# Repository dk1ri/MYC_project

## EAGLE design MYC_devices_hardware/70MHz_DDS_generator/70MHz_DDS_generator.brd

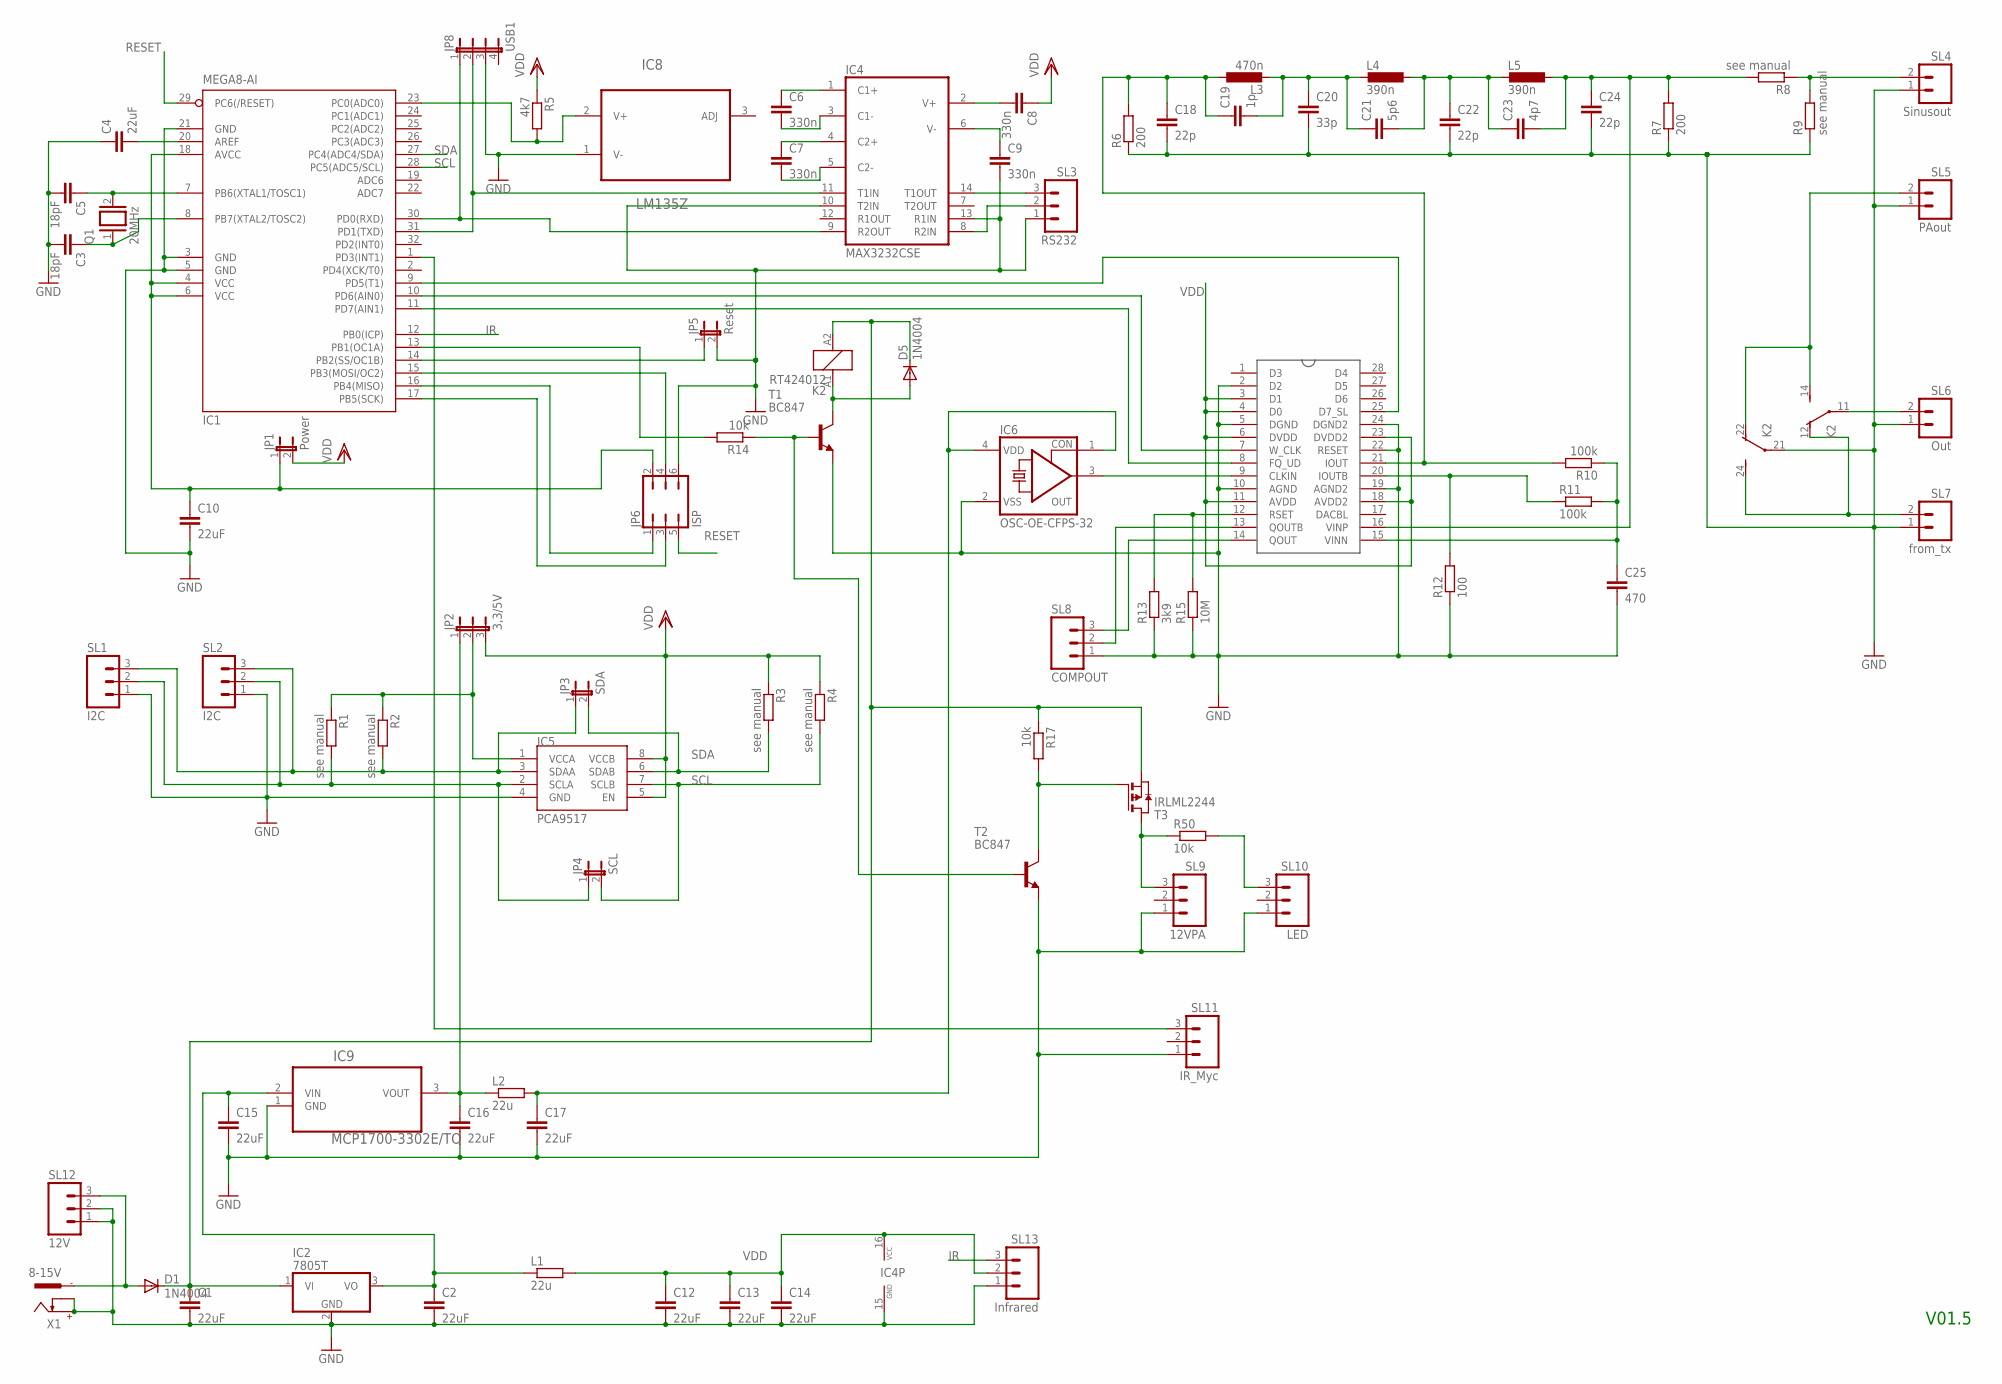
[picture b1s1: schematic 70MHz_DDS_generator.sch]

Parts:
C1, C2, C4, C10, C12, C13, C14, C15, C16, C17: 22uF; C1206
C3, C5: 18pF; C025-025X050
C6, C7, C8, C9: 330n; C1206
C18, C22, C24: 22p; C0805K
C19: 1p; C0805K
C20: 33p; C0805K
C21: 5p6; C0805K
C23: 4p7; C0805K
C25: 470; C1206
D1, D5: 1N4004; DO41-10
IC1: MEGA8-AI; TQFP32-08
IC2: 7805T; TO220H
IC4: MAX3232CSE; SO16
IC5: PCA9517; SO-08
IC6: OSC-OE-CFPS-32; 7.2X5.2-4-PAD
IC7: AD9851; SSOP28
IC8: LM135Z; TO127P254X533-3P
IC9: MCP1700-3302E/TO; TO127P254X495-3
JP1: Power; JP1
JP2: 3,3/5V; JP2
JP3: SDA; JP1
JP4: SCL; JP1
JP5: Reset; JP1
JP6: ISP; JP3Q
JP8: USB1; JP4
K2: RT424012; RT2C/O
L1, L2: 22u; R6332
L3: 470n; L4532M
L4, L5: 390n; L4532M
Q1: 20MHz; QS
R1, R2, R3, R4, R8, R9: see manual; R1206
R5: 4k7; R1206
R6, R7: 200; R1206
R10, R11: 100k; R1206
R12: 100; R1206
R13: 3k9; R1206
R14, R17, R50: 10k; R1206
R15: 10M; R1206
SL1, SL2: I2C; 03P
SL3: RS232; 03P
SL4: Sinusout; 02P
SL5: PAout; 02P
SL6: Out; 02P
SL7: from_tx; 02P
SL8: COMPOUT; 03P
SL9: 12VPA; 03P
SL10: LED; 03P
SL11: IR_Myc; 03P
SL12: 12V; 03P
SL13: Infrared; 03P
T1, T2: BC847; SOT23
T3: IRLML2244; SOT-23
X1: 8-15V; 737992-5

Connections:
GND: C1.2, C2.2, C3.2, C4.1, C5.2, C9.2, C10.2, C12.2, C13.2, C14.2, C15.2, C16.2, C17.2, C18.2, C20.2, C22.2, C24.2, C25.2, IC1.3 (GND), IC1.5 (GND), IC1.21 (GND), IC2.2 (GND), IC4.10 (T2IN), IC4.13 (R1IN), IC4.15 (GND), IC5.4 (GND), IC6.2 (VSS), IC7.2 (D2), IC7.5 (DGND), IC7.10 (AGND), IC7.19 (AGND2), IC7.22 (RESET), IC7.24 (DGND2), IC8.1 (V-), IC9.1 (GND), JP5.2, JP6.6, JP8.3, K2.21, R6.1, R7.1, R9.1, R12.1, R13.1, R15.1, SL1.1, SL2.1, SL3.1, SL4.1, SL5.1, SL6.1, SL7.1, SL8.1, SL9.1, SL10.1, SL11.1, SL12.1, SL12.2, SL13.1, T1.2 (E), T2.2 (E), X1.+, X1.K
IR: IC1.12 (PB0(ICP)), SL13.3
unnamed: IC1.9 (PD5(T1)), IC7.25 (D7_SL)
unnamed: C5.1, IC1.7 (PB6(XTAL1/TOSC1)), Q1.2
unnamed: C3.1, IC1.8 (PB7(XTAL2/TOSC2)), Q1.1
unnamed: C4.2, IC1.20 (AREF)
unnamed: IC5.3 (SDAA), JP3.1, R2.2, SL1.3, SL2.3
unnamed: IC1.16 (PB4(MISO)), JP6.1
unnamed: D1.A, SL12.3, X1.-1
unnamed: C10.1, IC1.4 (VCC), IC1.6 (VCC), IC1.18 (AVCC), JP1.1, JP6.2
unnamed: IC1.17 (PB5(SCK)), JP6.3
unnamed: IC1.14 (PB2(SS/OC1B)), JP5.1
unnamed: IC1.15 (PB3(MOSI/OC2)), JP6.4
unnamed: C7.2, IC4.5 (C2-)
unnamed: IC5.1 (VCCA), JP2.2, R1.1, R2.1
unnamed: IC5.2 (SCLA), JP4.1, R1.2, SL1.2, SL2.2
unnamed: IC4.14 (T1OUT), SL3.3
unnamed: C8.2, IC4.2 (V+)
unnamed: K2.12 (O), K2.24 (S), SL7.2
unnamed: C2.1, C15.1, IC2.3 (VO), IC9.2 (VIN), L1.1
unnamed: IC1.10 (PD6(AIN0)), IC7.7 (W_CLK)
unnamed: IC4.8 (R2IN), SL3.2
unnamed: R50.2, SL10.3
unnamed: C7.1, IC4.4 (C2+)
unnamed: K2.14 (S), K2.22 (O), SL5.2
unnamed: C21.2, C22.1, C23.1, L4.1, L5.2
unnamed: C17.1, IC6.1 (CON), IC6.4 (VDD), L2.2
unnamed: C18.1, C19.1, IC7.21 (IOUT), L3.1, R6.2, R10.2
unnamed: C19.2, C20.1, C21.1, L3.2, L4.2
unnamed: C9.1, IC4.6 (V-)
unnamed: IC1.11 (PD7(AIN1)), IC7.8 (FQ_UD)
unnamed: IC6.3 (OUT), IC7.9 (CLKIN)
unnamed: R14.1, T1.1 (B), T2.1 (B)
unnamed: C23.2, C24.1, IC7.16 (VINP), L5.1, R7.2, R8.2
unnamed: IC1.30 (PD0(RXD)), IC4.9 (R2OUT), JP8.1
unnamed: D5.A, K2.A1 (1), T1.3 (C)
unnamed: IC7.12 (RSET), R13.2, R15.2
unnamed: C25.1, IC7.15 (VINN), R10.1, R11.2
unnamed: IC7.14 (QOUT), SL8.3
unnamed: IC1.23 (PC0(ADC0)), IC8.2 (V+), R5.2
unnamed: IC7.20 (IOUTB), R11.1, R12.2
unnamed: K2.11, SL6.2
unnamed: R50.1, SL9.3, T3.1 (D)
unnamed: R17.2, T2.3 (C), T3.3 (G)
unnamed: IC1.31 (PD1(TXD)), IC4.11 (T1IN), JP8.2
unnamed: IC1.13 (PB1(OC1A)), R14.2
unnamed: C1.1, D1.C, D5.C, IC2.1 (VI), K2.A2 (2), R17.1, T3.2 (S)
unnamed: IC1.1 (PD3(INT1)), SL11.3
unnamed: C6.1, IC4.1 (C1+)
unnamed: IC7.13 (QOUTB), SL8.2
unnamed: R8.1, R9.2, SL4.2
unnamed: C6.2, IC4.3 (C1-)
unnamed: C16.1, IC9.3 (VOUT), JP2.1, L2.1
RESET: IC1.29 (PC6(/RESET)), JP6.5
SCL: IC1.28 (PC5(ADC5/SCL)), IC5.7 (SCLB), JP4.2, R4.2
SDA: IC1.27 (PC4(ADC4/SDA)), IC5.6 (SDAB), JP3.2, R3.2
VDD: C8.1, C12.1, C13.1, C14.1, IC4.16 (VCC), IC5.5 (EN), IC5.8 (VCCB), IC7.3 (D1), IC7.4 (D0), IC7.6 (DVDD), IC7.11 (AVDD), IC7.18 (AVDD2), IC7.23 (DVDD2), JP1.2, JP2.3, L1.2, R3.1, R4.1, R5.1, SL13.2

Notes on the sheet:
V01.5

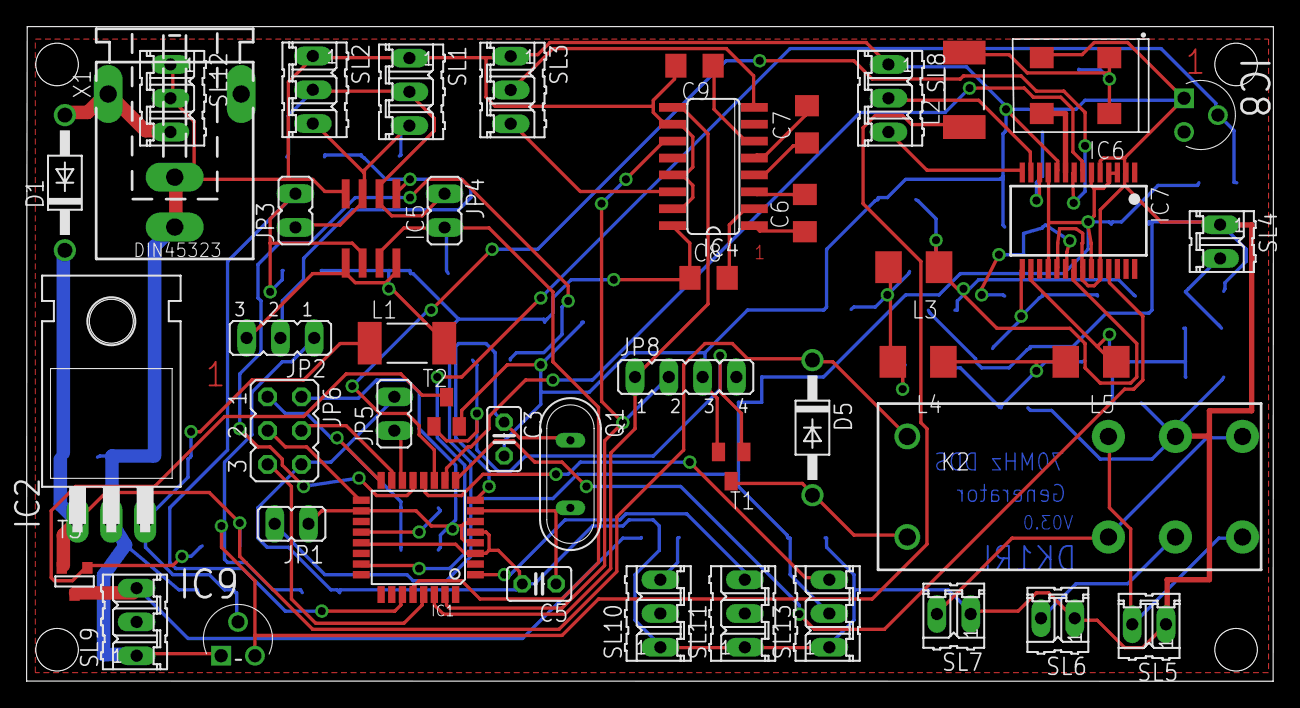
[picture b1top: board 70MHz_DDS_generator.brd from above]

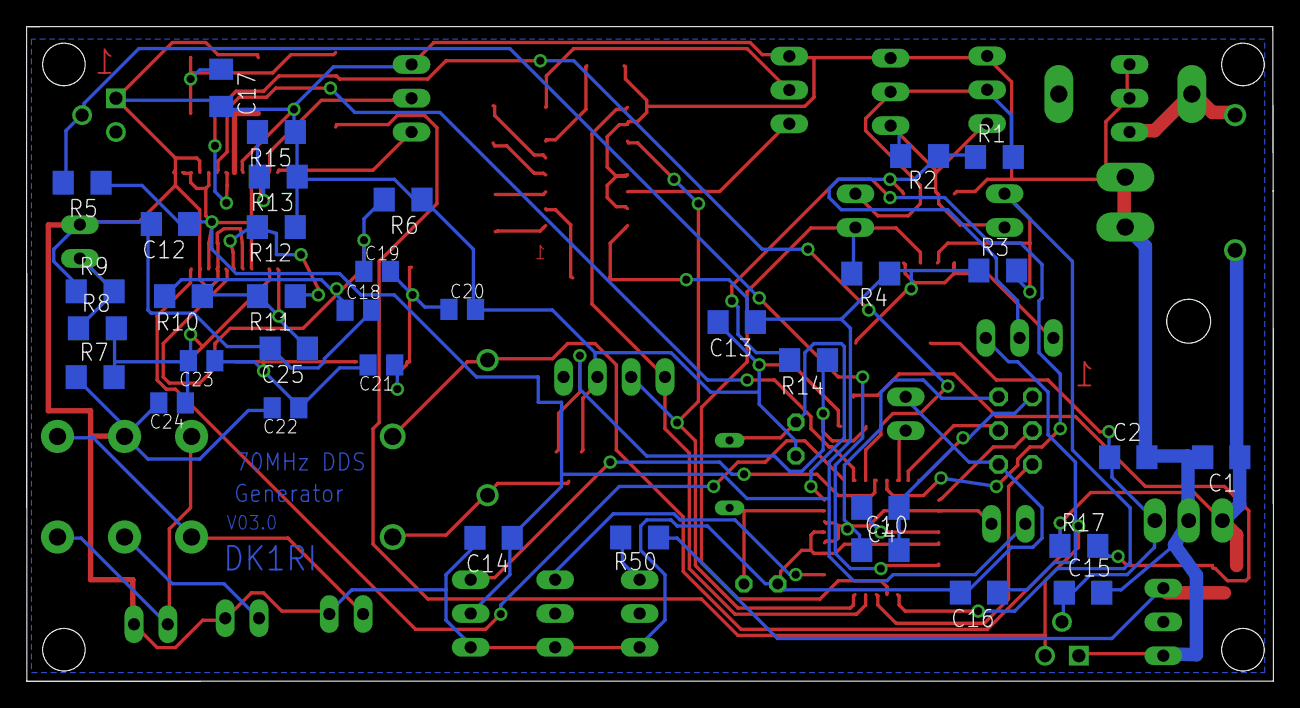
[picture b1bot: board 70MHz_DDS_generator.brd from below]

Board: 3 copper layers, 93.7 x 49.2 mm, 82 parts (35 on the bottom side), 57 nets.

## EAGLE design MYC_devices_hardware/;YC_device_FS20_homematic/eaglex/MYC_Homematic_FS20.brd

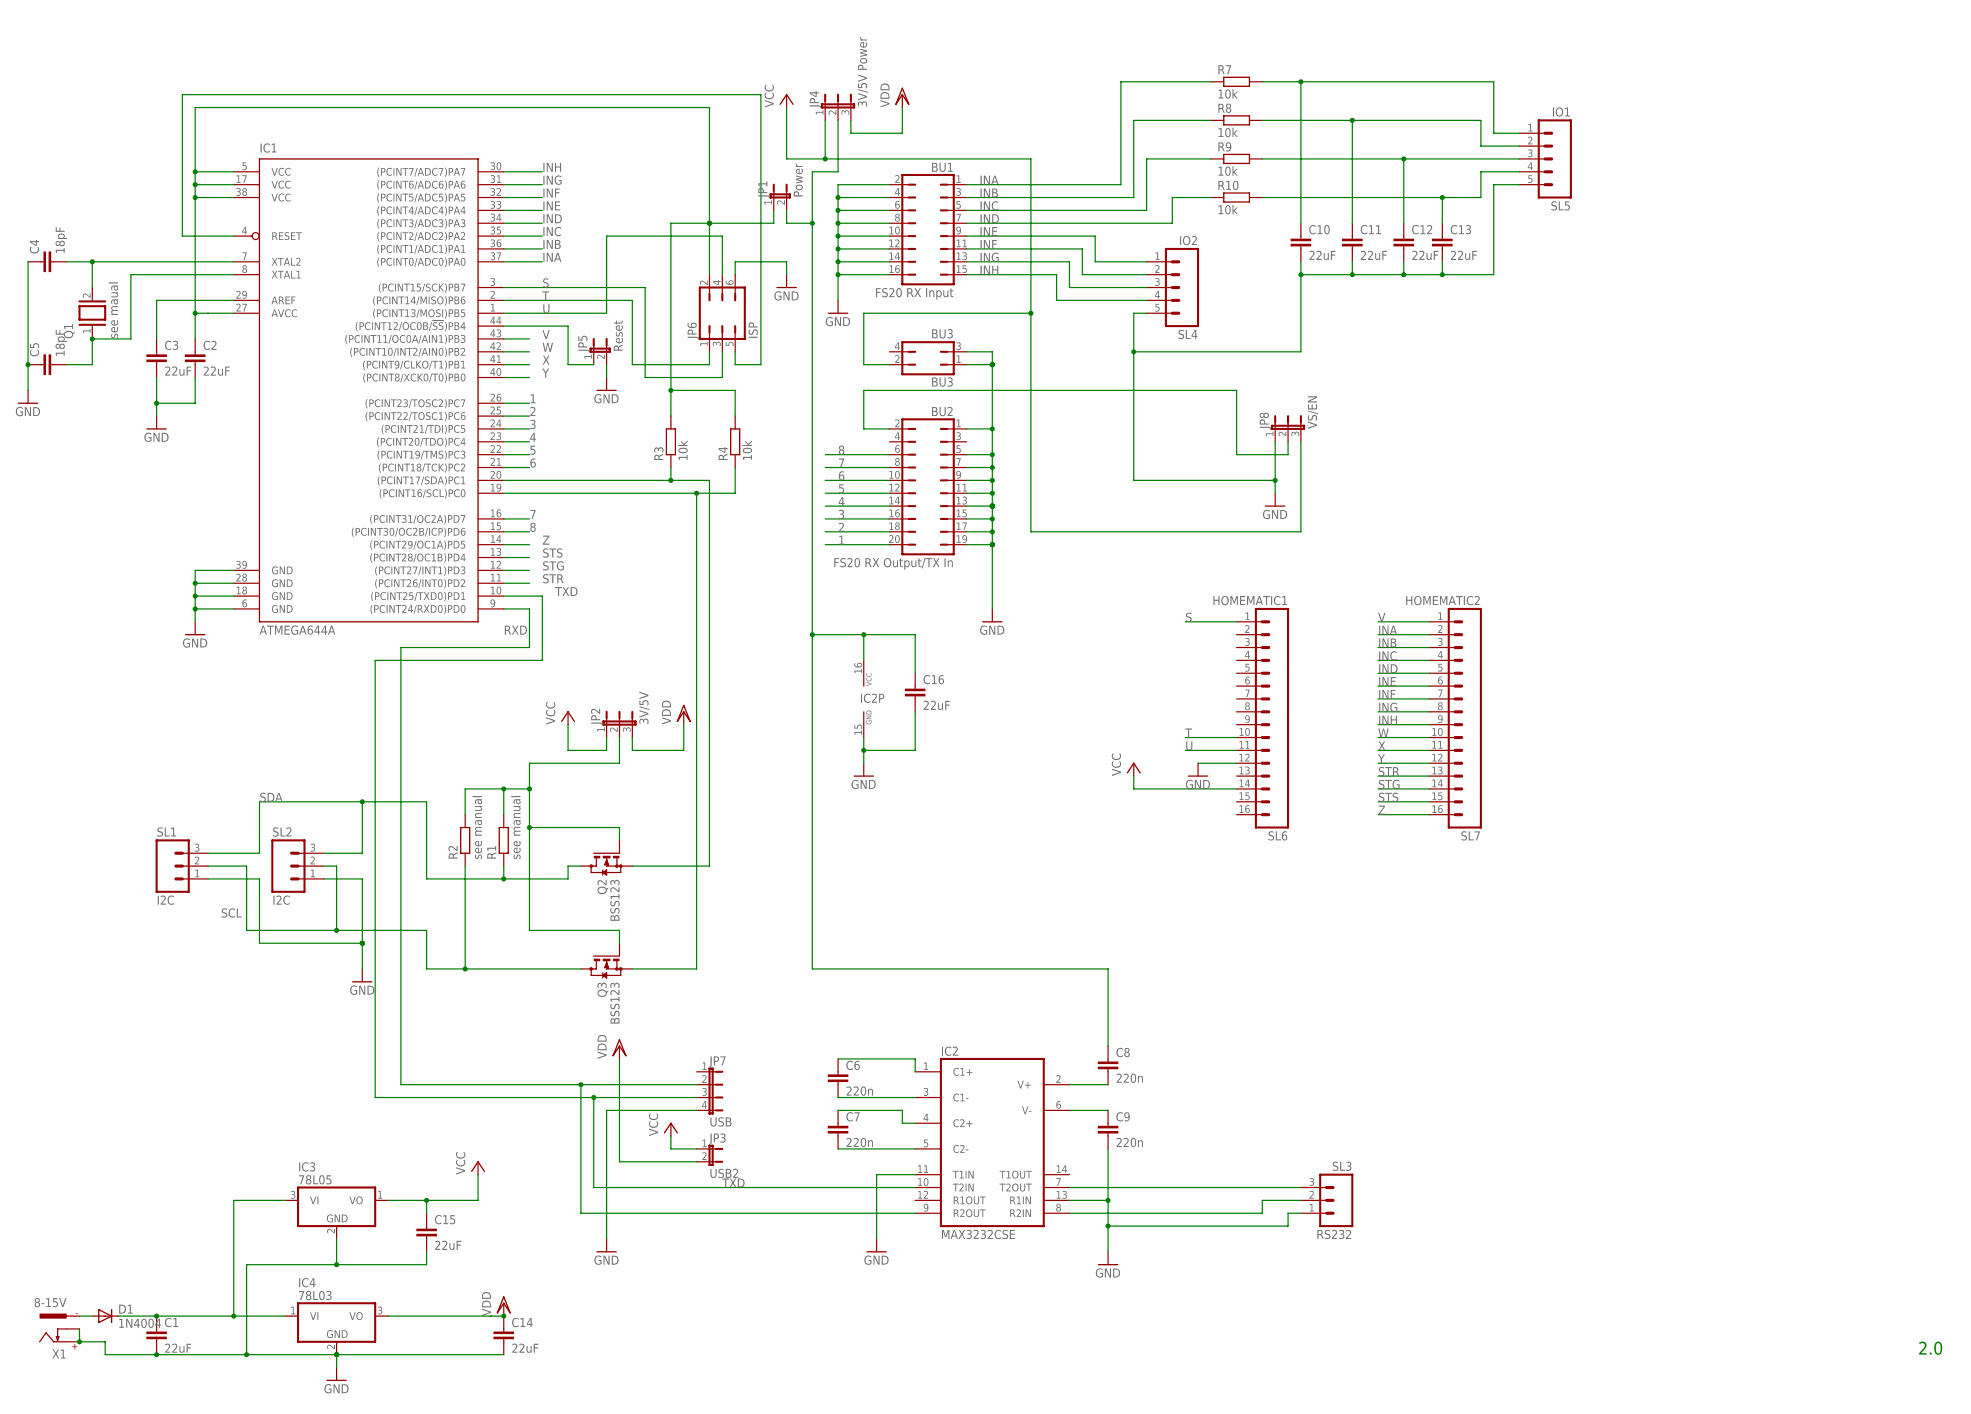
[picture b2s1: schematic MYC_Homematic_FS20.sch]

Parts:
BU1: FS20 RX Input; JP8Q
BU2: FS20 RX Output/TX In; JP10Q
BU3: BU3; JP2Q
C1, C2, C3, C10, C11, C12, C13, C14, C15, C16: 22uF; C1206
C4, C5: 18pF; C025-030X050
C6, C7, C8, C9: 220n; C1206
D1: 1N4004; DO41-10
IC1: ATMEGA644A; TQFP44
IC2: MAX3232CSE; SO16
IC3: 78L05; TO92
IC4: 78L03; TO220V
JP1: Power; JP1
JP2: 3V/5V; JP2
JP3: USB2; JP1
JP4: 3V/5V Power; JP2
JP5: Reset; JP1
JP6: ISP; JP3Q
JP7: USB; JP4
JP8: VS/EN; JP2
Q1: see maual; QS
Q2, Q3: BSS123; SOT23
R1, R2: see manual; R1206
R3, R4, R7, R8, R9, R10: 10k; R1206
SL1, SL2: I2C; 03P
SL3: RS232; 03P
SL4: IO2; 05P
SL5: IO1; 05P
SL6: HOMEMATIC1; 16P
SL7: HOMEMATIC2; 16P
X1: 8-15V; 737992-5

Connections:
1: BU2.20, IC1.26 ((PCINT23/TOSC2)PC7)
2: BU2.18, IC1.25 ((PCINT22/TOSC1)PC6)
3: BU2.16, IC1.24 ((PCINT21/TDI)PC5)
4: BU2.14, IC1.23 ((PCINT20/TDO)PC4)
5: BU2.12, IC1.22 ((PCINT19/TMS)PC3)
6: BU2.10, IC1.21 ((PCINT18/TCK)PC2)
7: BU2.8, IC1.16 ((PCINT31/OC2A)PD7)
8: BU2.6, IC1.15 ((PCINT30/OC2B/ICP)PD6)
C13: C6.1, IC2.1 (C1+)
GND: BU1.2, BU1.4, BU1.6, BU1.8, BU1.10, BU1.12, BU1.14, BU1.16, BU2.1, BU2.5, BU2.7, BU2.9, BU2.11, BU2.13, BU2.15, BU2.17, BU2.19, BU3.1, BU3.3, C1.2, C2.2, C3.2, C4.1, C5.1, C9.2, C10.2, C11.2, C12.2, C13.2, C14.2, C15.2, C16.2, IC1.6 (GND), IC1.18 (GND), IC1.28 (GND), IC1.39 (GND), IC2.11 (T1IN), IC2.13 (R1IN), IC2.15 (GND), IC3.2 (GND), IC4.2 (GND), JP5.2, JP6.6, JP7.4, JP8.1, SL1.1, SL2.1, SL3.1, SL4.5, SL5.5, SL6.12, X1.+, X1.K
INA: BU1.1, IC1.37 ((PCINT0/ADC0)PA0), R7.1, SL7.2
INB: BU1.3, IC1.36 ((PCINT1/ADC1)PA1), R8.1, SL7.3
INC: BU1.5, IC1.35 ((PCINT2/ADC2)PA2), R9.1, SL7.4
IND: BU1.7, IC1.34 ((PCINT3/ADC3)PA3), R10.1, SL7.5
INE: BU1.9, IC1.33 ((PCINT4/ADC4)PA4), SL4.1, SL7.6
INF: BU1.11, IC1.32 ((PCINT5/ADC5)PA5), SL4.2, SL7.7
ING: BU1.13, IC1.31 ((PCINT6/ADC6)PA6), SL4.3, SL7.8
INH: BU1.15, IC1.30 ((PCINT7/ADC7)PA7), SL4.4, SL7.9
unnamed: C1.1, D1.C, IC3.3 (VI), IC4.1 (VI)
unnamed: IC1.44 ((PCINT12/OC0B/!SS!)PB4), JP5.1
unnamed: C7.2, IC2.5 (C2-)
unnamed: JP2.2, Q2.1 (G), Q3.1 (G), R1.2, R2.2
unnamed: IC1.19 ((PCINT16/SCL)PC0), Q3.2 (S), R4.1
unnamed: C3.1, IC1.29 (AREF)
unnamed: C2.1, IC1.5 (VCC), IC1.17 (VCC), IC1.27 (AVCC), IC1.38 (VCC), JP1.1, JP6.2, R3.2, R4.2
unnamed: IC1.20 ((PCINT17/SDA)PC1), Q2.2 (S), R3.1
unnamed: BU2.2, JP8.2
unnamed: D1.A, X1.-1
unnamed: IC2.8 (R2IN), SL3.2
unnamed: C7.1, IC2.4 (C2+)
unnamed: C6.2, IC2.3 (C1-)
unnamed: C10.1, R7.2, SL5.1
unnamed: C8.2, IC2.2 (V+)
unnamed: C9.1, IC2.6 (V-)
unnamed: C11.1, R8.2, SL5.2
unnamed: C4.2, IC1.7 (XTAL2), Q1.2
unnamed: C12.1, R9.2, SL5.3
unnamed: C13.1, R10.2, SL5.4
unnamed: C8.1, C16.1, IC2.16 (VCC), JP1.2, JP4.2
unnamed: IC1.4 (RESET), JP6.5
unnamed: IC2.7 (T2OUT), SL3.3
unnamed: C5.2, IC1.8 (XTAL1), Q1.1
RXD: IC1.9 ((PCINT24/RXD0)PD0), IC2.9 (R2OUT), JP7.2
S: IC1.3 ((PCINT15/SCK)PB7), JP6.3, SL6.1
SCL: Q3.3 (D), R2.1, SL1.2, SL2.2
SDA: Q2.3 (D), R1.1, SL1.3, SL2.3
STG: IC1.12 ((PCINT27/INT1)PD3), SL7.14
STR: IC1.11 ((PCINT26/INT0)PD2), SL7.13
STS: IC1.13 ((PCINT28/OC1B)PD4), SL7.15
T: IC1.2 ((PCINT14/MISO)PB6), JP6.1, SL6.10
TXD: IC1.10 ((PCINT25/TXD0)PD1), IC2.10 (T2IN), JP7.3
U: IC1.1 ((PCINT13/MOSI)PB5), JP6.4, SL6.11
V: IC1.43 ((PCINT11/OC0A/AIN1)PB3), SL7.1
VCC: BU3.2, C15.1, IC3.1 (VO), JP2.1, JP3.1, JP4.1, JP8.3, SL6.14
VDD: C14.1, IC4.3 (VO), JP2.3, JP3.2, JP4.3
W: IC1.42 ((PCINT10/INT2/AIN0)PB2), SL7.10
X: IC1.41 ((PCINT9/CLKO/T1)PB1), SL7.11
Y: IC1.40 ((PCINT8/XCK0/T0)PB0), SL7.12
Z: IC1.14 ((PCINT29/OC1A)PD5), SL7.16

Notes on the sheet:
2.0

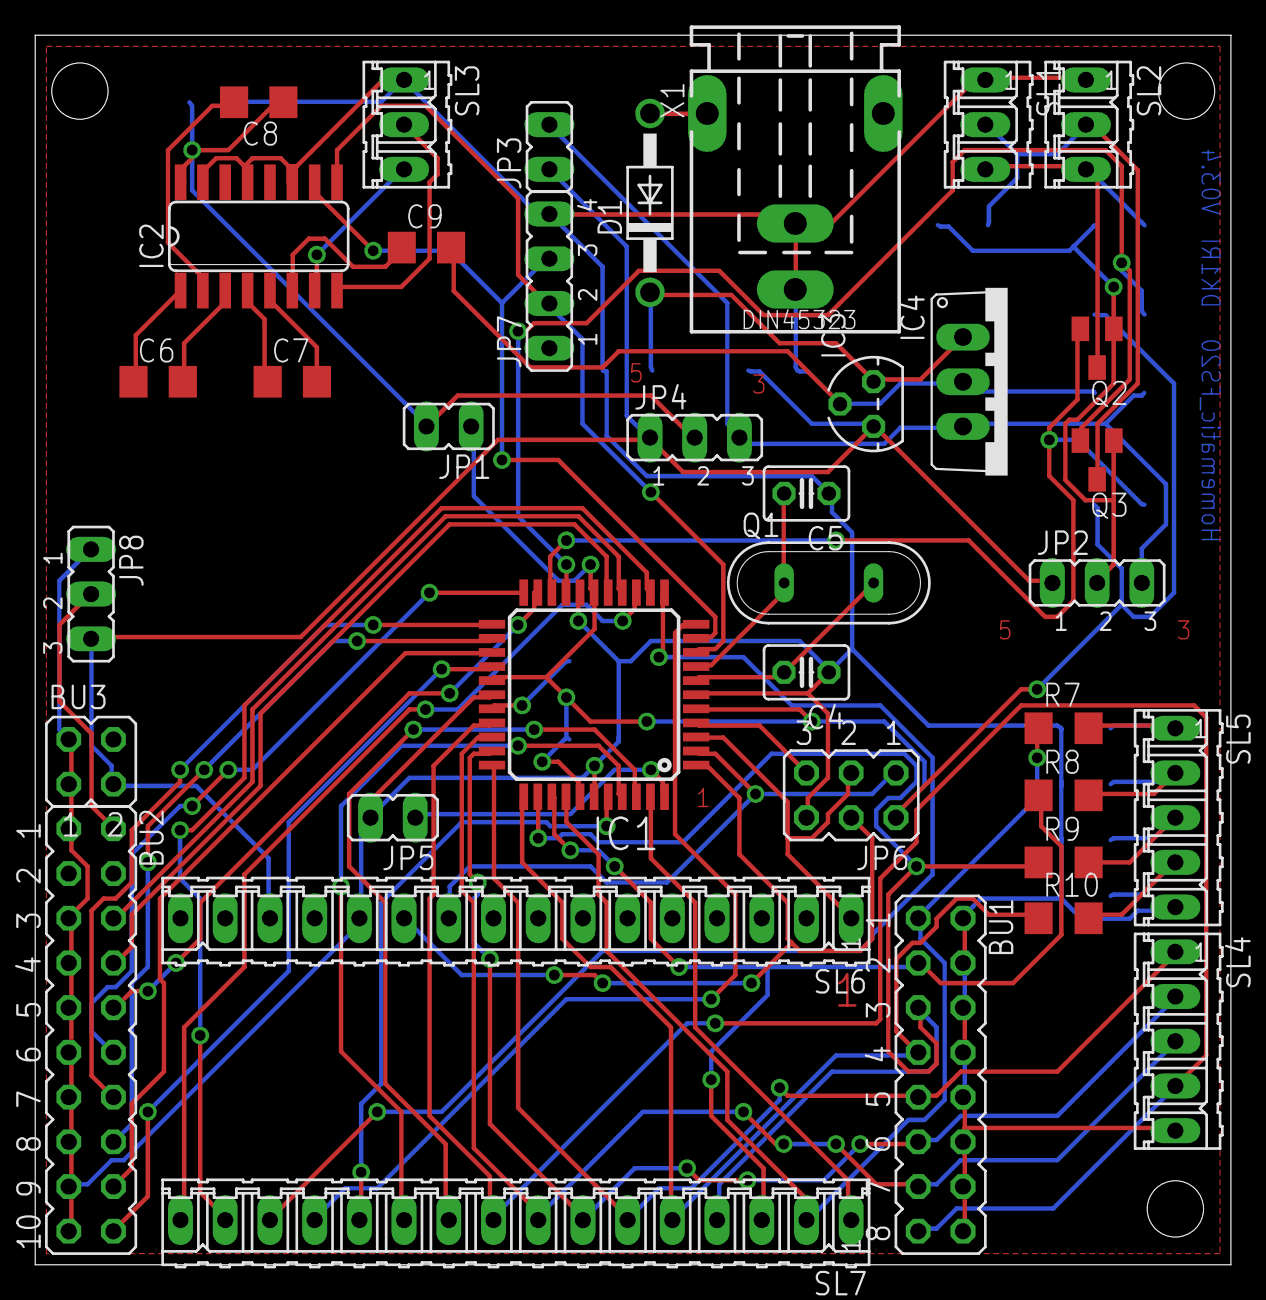
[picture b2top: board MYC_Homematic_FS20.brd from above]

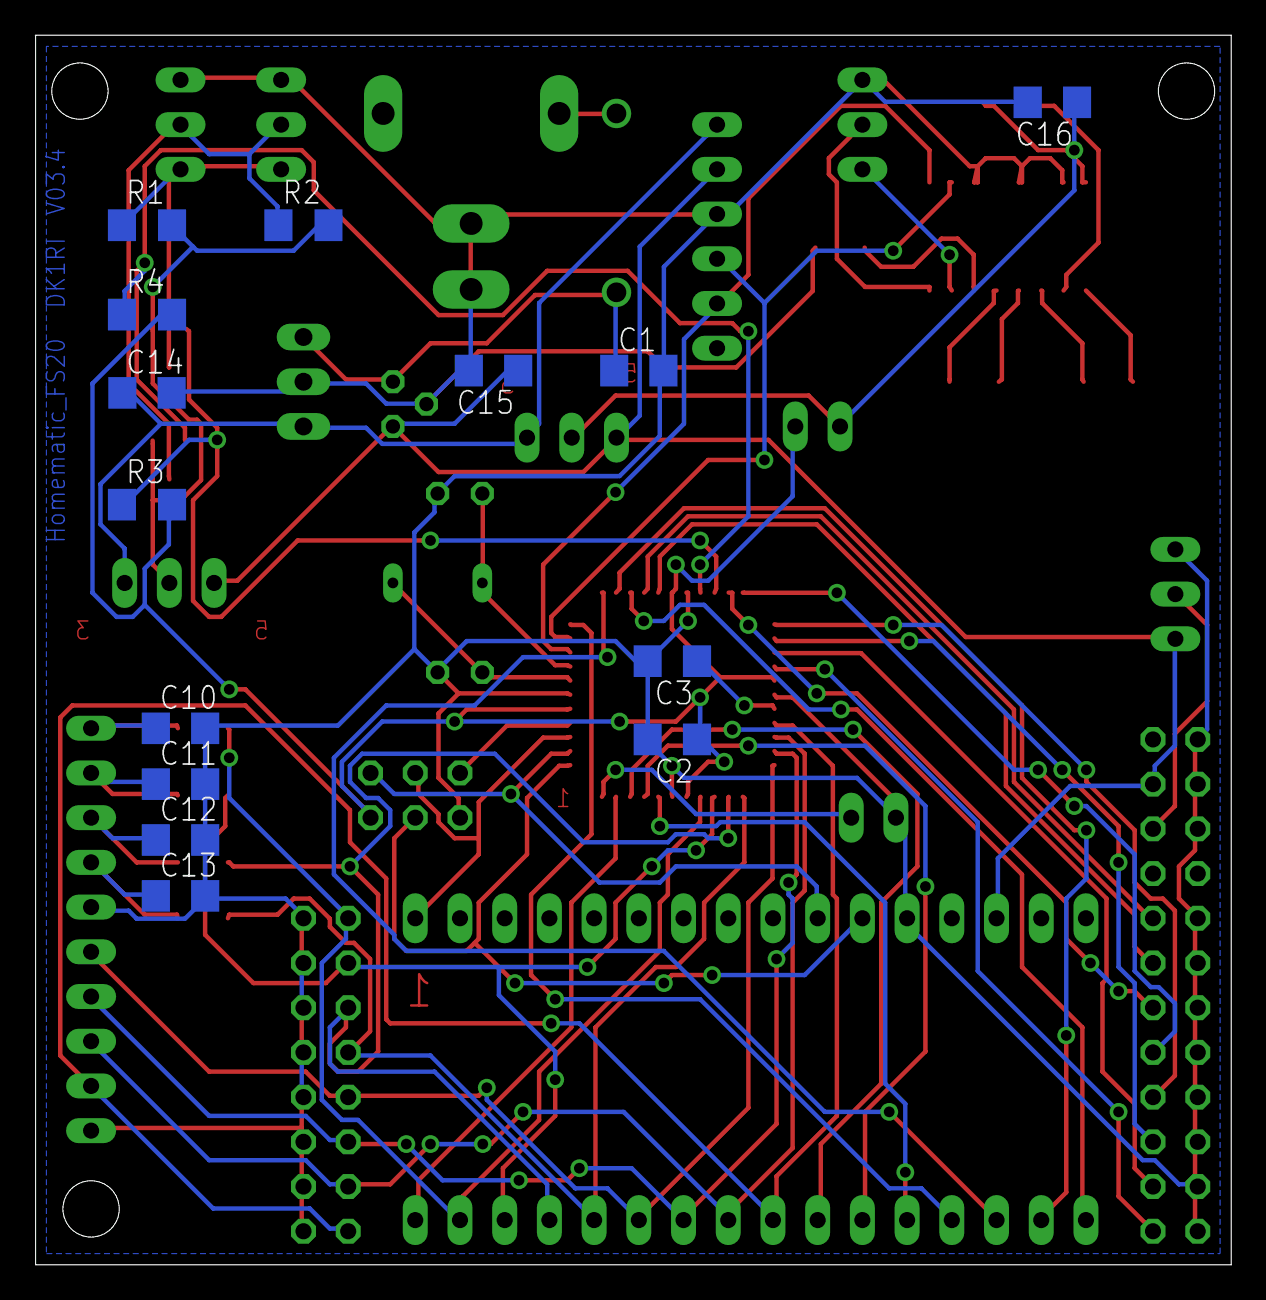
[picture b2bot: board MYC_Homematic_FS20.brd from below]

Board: 2 copper layers, 67.9 x 69.8 mm, 51 parts (14 on the bottom side), 59 nets.

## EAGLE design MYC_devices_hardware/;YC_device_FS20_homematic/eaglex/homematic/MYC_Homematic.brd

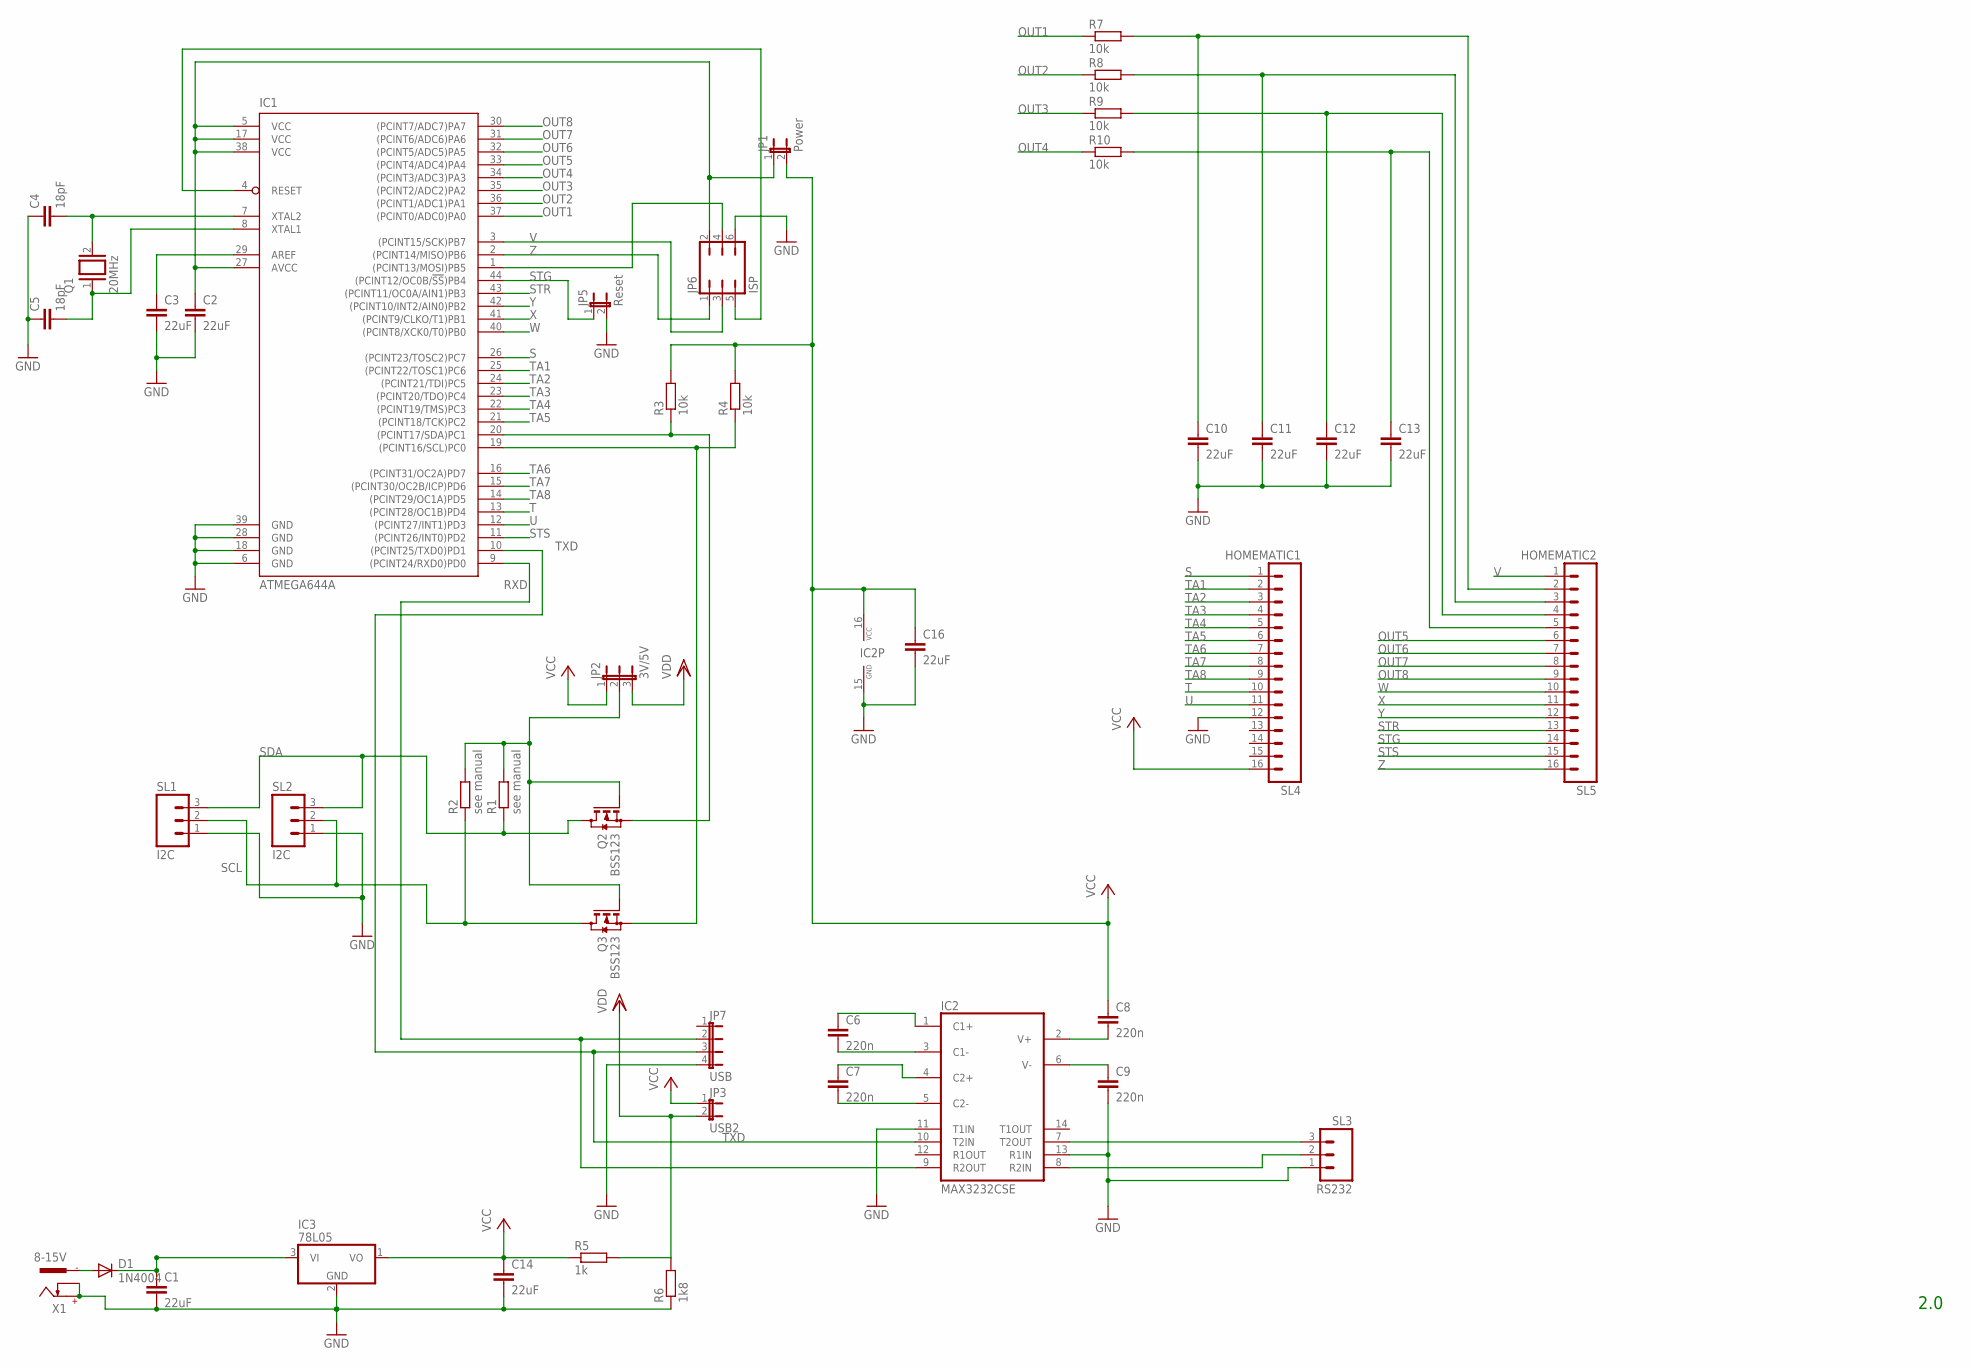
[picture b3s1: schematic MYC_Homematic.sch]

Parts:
C1, C2, C3, C10, C11, C12, C13, C14, C16: 22uF; C1206
C4, C5: 18pF; C025-030X050
C6, C7, C8, C9: 220n; C1206
D1: 1N4004; DO41-10
IC1: ATMEGA644A; TQFP44
IC2: MAX3232CSE; SO16
IC3: 78L05; TO92
JP1: Power; JP1
JP2: 3V/5V; JP2
JP3: USB2; JP1
JP5: Reset; JP1
JP6: ISP; JP3Q
JP7: USB; JP4
Q1: 20MHz; QS
Q2, Q3: BSS123; SOT23
R1, R2: see manual; R1206
R3, R4, R7, R8, R9, R10: 10k; R1206
R5: 1k; R1206
R6: 1k8; R1206
SL1, SL2: I2C; 03P
SL3: RS232; 03P
SL4: HOMEMATIC1; 16P
SL5: HOMEMATIC2; 16P
X1: 8-15V; 737992-5

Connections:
C13: C6.1, IC2.1 (C1+)
GND: C1.2, C2.2, C3.2, C4.1, C5.1, C9.2, C10.2, C11.2, C12.2, C13.2, C14.2, C16.2, IC1.6 (GND), IC1.18 (GND), IC1.28 (GND), IC1.39 (GND), IC2.11 (T1IN), IC2.13 (R1IN), IC2.15 (GND), IC3.2 (GND), JP5.2, JP6.6, JP7.4, R6.1, SL1.1, SL2.1, SL3.1, SL4.12, X1.+, X1.K
unnamed: C1.1, D1.C, IC3.3 (VI)
unnamed: C7.2, IC2.5 (C2-)
unnamed: JP2.2, Q2.1 (G), Q3.1 (G), R1.2, R2.2
unnamed: IC1.19 ((PCINT16/SCL)PC0), Q3.2 (S), R4.1
unnamed: C3.1, IC1.29 (AREF)
unnamed: C2.1, IC1.5 (VCC), IC1.17 (VCC), IC1.27 (AVCC), IC1.38 (VCC), JP1.1, JP6.2
unnamed: IC1.20 ((PCINT17/SDA)PC1), Q2.2 (S), R3.1
unnamed: D1.A, X1.-1
unnamed: IC2.8 (R2IN), SL3.2
unnamed: IC1.1 ((PCINT13/MOSI)PB5), JP6.4
unnamed: C7.1, IC2.4 (C2+)
unnamed: C6.2, IC2.3 (C1-)
unnamed: C10.1, R7.2, SL5.2
unnamed: C8.2, IC2.2 (V+)
unnamed: C9.1, IC2.6 (V-)
unnamed: C4.2, IC1.7 (XTAL2), Q1.2
unnamed: C11.1, R8.2, SL5.3
unnamed: C12.1, R9.2, SL5.4
unnamed: C13.1, R10.2, SL5.5
unnamed: IC1.4 (RESET), JP6.5
unnamed: IC2.7 (T2OUT), SL3.3
unnamed: C5.2, IC1.8 (XTAL1), Q1.1
OUT1: IC1.37 ((PCINT0/ADC0)PA0), R7.1
OUT2: IC1.36 ((PCINT1/ADC1)PA1), R8.1
OUT3: IC1.35 ((PCINT2/ADC2)PA2), R9.1
OUT4: IC1.34 ((PCINT3/ADC3)PA3), R10.1
OUT5: IC1.33 ((PCINT4/ADC4)PA4), SL5.6
OUT6: IC1.32 ((PCINT5/ADC5)PA5), SL5.7
OUT7: IC1.31 ((PCINT6/ADC6)PA6), SL5.8
OUT8: IC1.30 ((PCINT7/ADC7)PA7), SL5.9
RXD: IC1.9 ((PCINT24/RXD0)PD0), IC2.9 (R2OUT), JP7.2
S: IC1.26 ((PCINT23/TOSC2)PC7), SL4.1
SCL: Q3.3 (D), R2.1, SL1.2, SL2.2
SDA: Q2.3 (D), R1.1, SL1.3, SL2.3
STG: IC1.44 ((PCINT12/OC0B/!SS!)PB4), JP5.1, SL5.14
STR: IC1.43 ((PCINT11/OC0A/AIN1)PB3), SL5.13
STS: IC1.11 ((PCINT26/INT0)PD2), SL5.15
T: IC1.13 ((PCINT28/OC1B)PD4), SL4.10
TA1: IC1.25 ((PCINT22/TOSC1)PC6), SL4.2
TA2: IC1.24 ((PCINT21/TDI)PC5), SL4.3
TA3: IC1.23 ((PCINT20/TDO)PC4), SL4.4
TA4: IC1.22 ((PCINT19/TMS)PC3), SL4.5
TA5: IC1.21 ((PCINT18/TCK)PC2), SL4.6
TA6: IC1.16 ((PCINT31/OC2A)PD7), SL4.7
TA7: IC1.15 ((PCINT30/OC2B/ICP)PD6), SL4.8
TA8: IC1.14 ((PCINT29/OC1A)PD5), SL4.9
TXD: IC1.10 ((PCINT25/TXD0)PD1), IC2.10 (T2IN), JP7.3
U: IC1.12 ((PCINT27/INT1)PD3), SL4.11
V: IC1.3 ((PCINT15/SCK)PB7), JP6.3, SL5.1
VCC: C8.1, C14.1, C16.1, IC2.16 (VCC), IC3.1 (VO), JP1.2, JP2.1, JP3.1, R3.2, R4.2, R5.1, SL4.16
VDD: JP2.3, JP3.2, R5.2, R6.2
W: IC1.40 ((PCINT8/XCK0/T0)PB0), SL5.10
X: IC1.41 ((PCINT9/CLKO/T1)PB1), SL5.11
Y: IC1.42 ((PCINT10/INT2/AIN0)PB2), SL5.12
Z: IC1.2 ((PCINT14/MISO)PB6), JP6.1, SL5.16

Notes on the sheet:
2.0

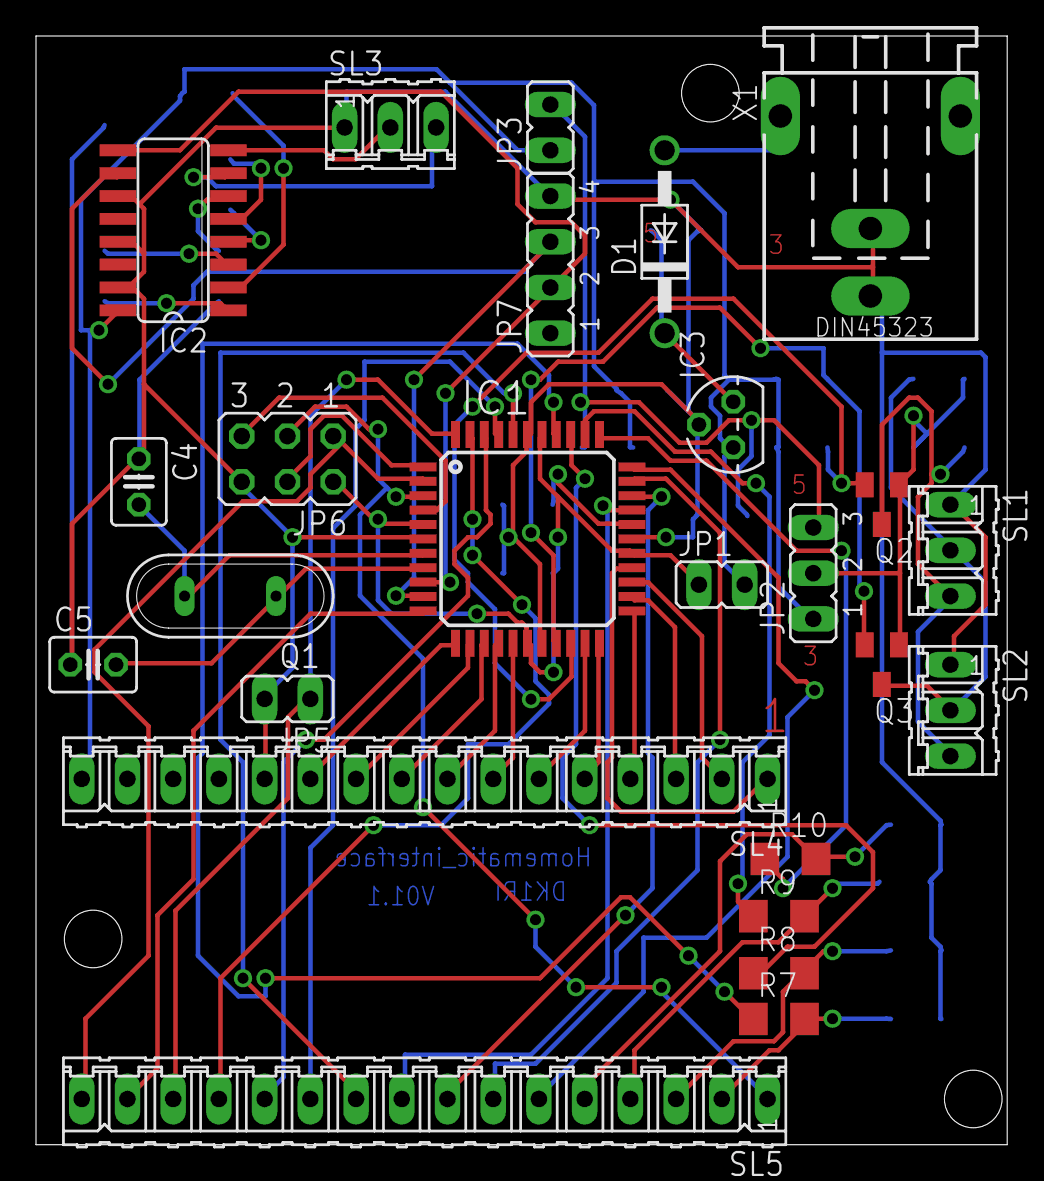
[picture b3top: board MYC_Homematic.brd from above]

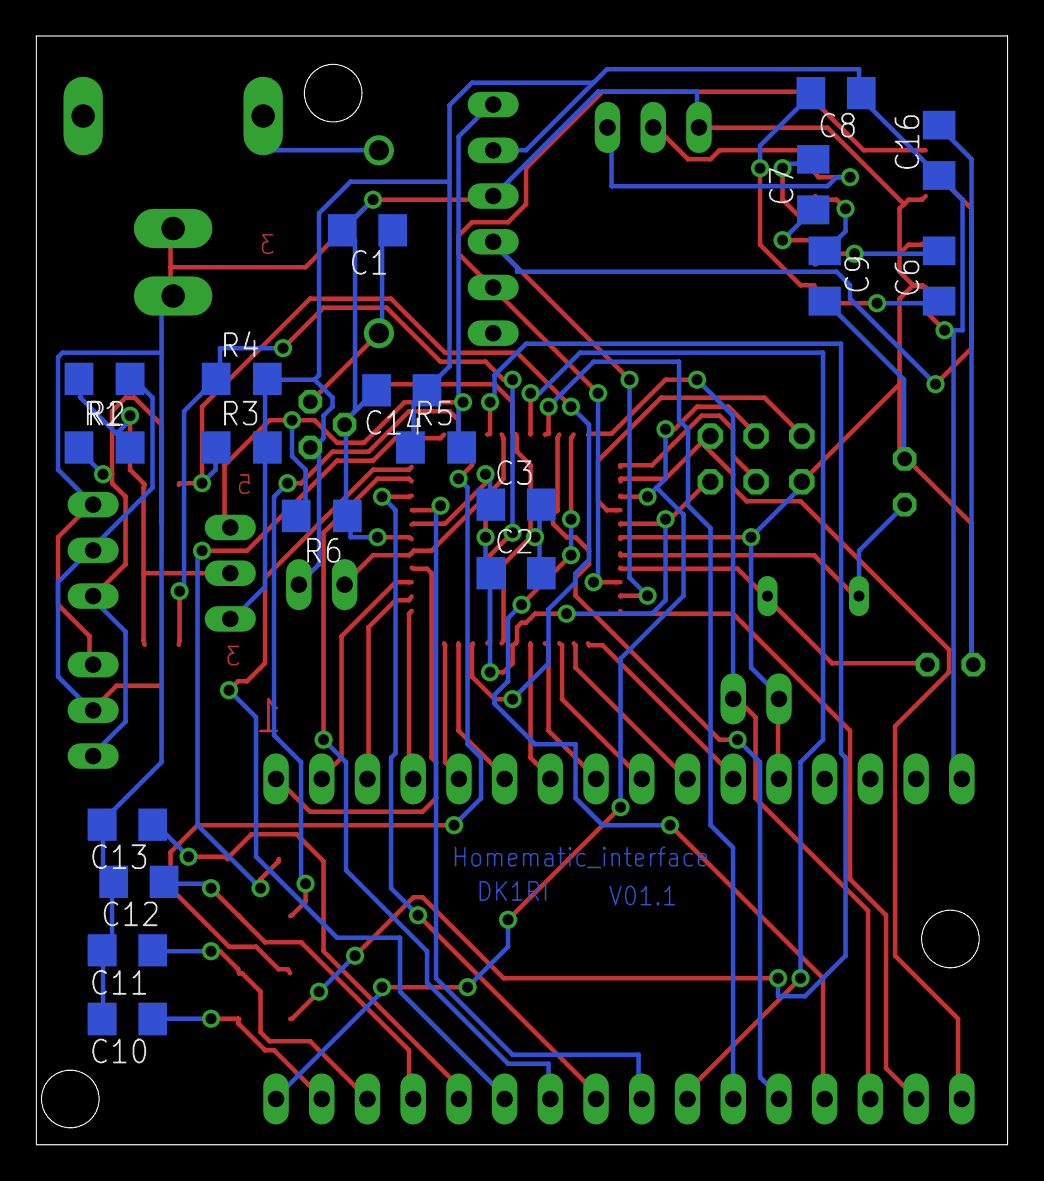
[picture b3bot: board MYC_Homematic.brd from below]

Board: 2 copper layers, 54.0 x 61.6 mm, 44 parts (19 on the bottom side), 57 nets.
